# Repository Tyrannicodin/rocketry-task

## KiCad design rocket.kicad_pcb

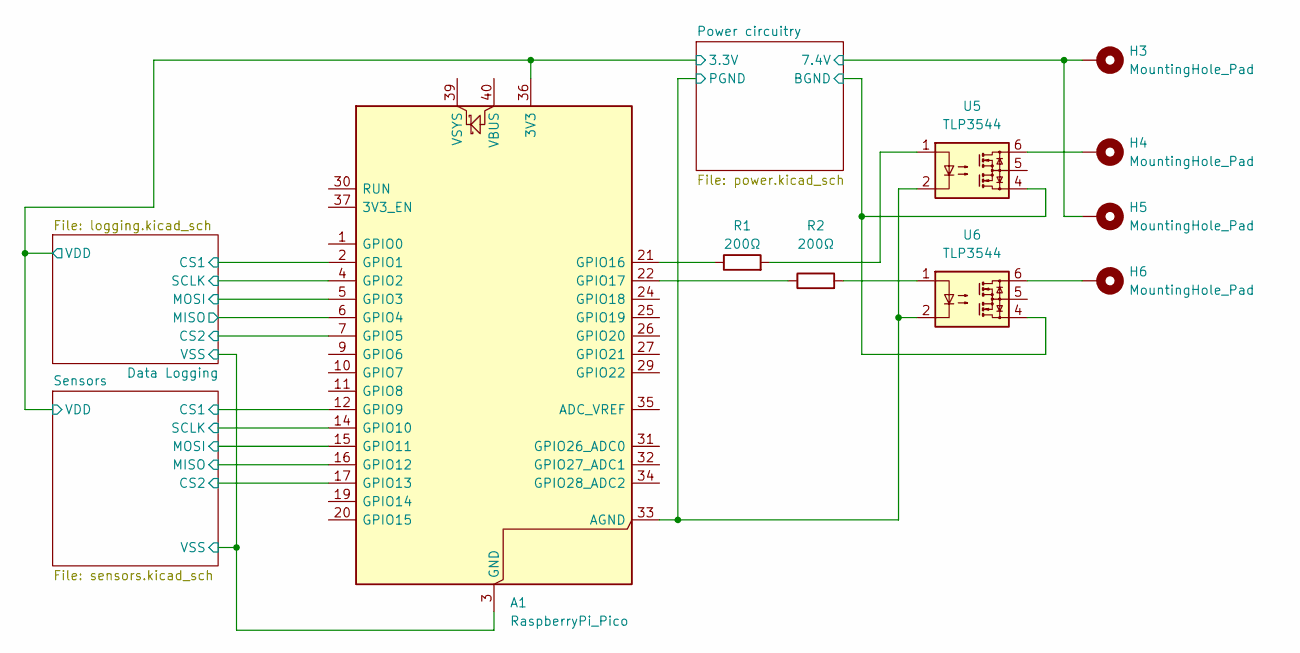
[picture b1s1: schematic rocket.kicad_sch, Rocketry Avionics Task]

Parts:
A1: RaspberryPi_Pico; RaspberryPi_Pico_Common_Unspecified
H3, H4, H5, H6: MountingHole_Pad; MountingHole_2.5mm_Pad
R1, R2: 200Ω; R_0201_0603Metric
U5, U6: TLP3544; DIP-6_W7.62mm

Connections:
/Data Logging/CS1: A1.2 (GPIO1); also elsewhere on the board
/Data Logging/CS2: A1.7 (GPIO5); also elsewhere on the board
/Data Logging/MISO: A1.6 (GPIO4); also elsewhere on the board
/Data Logging/MOSI: A1.5 (GPIO3); also elsewhere on the board
/Data Logging/SCLK: A1.4 (GPIO2); also elsewhere on the board
/Data Logging/VDD: A1.36 (3V3); also elsewhere on the board
/Data Logging/VSS: A1.3 (GND), A1.8 (GND), A1.13 (GND), A1.18 (GND), A1.23 (GND), A1.28 (GND), A1.38 (GND); also elsewhere on the board
/Power circuitry/7.4V: H3.1, H5.1; also elsewhere on the board
/Power circuitry/BGND: U5.4, U6.4; also elsewhere on the board
/Power circuitry/PGND: A1.33 (AGND), U5.2, U6.2; also elsewhere on the board
/Sensors/CS1: A1.12 (GPIO9); also elsewhere on the board
/Sensors/CS2: A1.17 (GPIO13); also elsewhere on the board
/Sensors/MISO: A1.16 (GPIO12); also elsewhere on the board
/Sensors/MOSI: A1.15 (GPIO11); also elsewhere on the board
/Sensors/SCLK: A1.14 (GPIO10); also elsewhere on the board
unnamed: A1.21 (GPIO16), R1.1
unnamed: A1.22 (GPIO17), R2.1
unnamed: H4.1, U5.6
unnamed: H6.1, U6.6
unnamed: R1.2, U5.1
unnamed: R2.2, U6.1

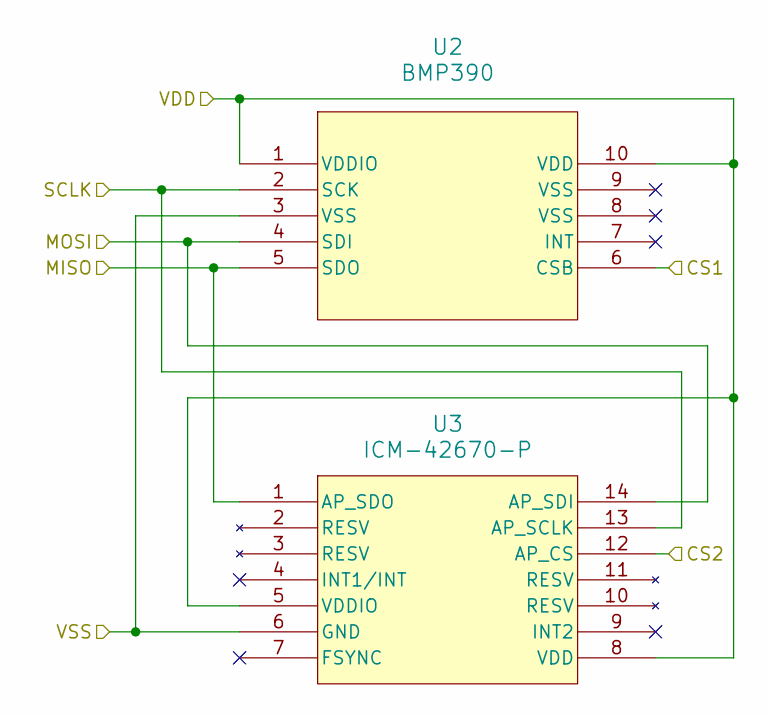
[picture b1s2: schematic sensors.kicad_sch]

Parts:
U2: BMP390; 10LGA_2X2X0p75_BOS
U3: ICM-42670-P; LGA14_2.5X3X0.76_IVS

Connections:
/Data Logging/VDD: U2.1 (VDDIO), U2.10 (VDD), U3.5 (VDDIO), U3.8 (VDD); also elsewhere on the board
/Data Logging/VSS: U2.3 (VSS), U3.6 (GND); also elsewhere on the board
/Sensors/CS1: U2.6 (CSB); also elsewhere on the board
/Sensors/CS2: U3.12 (AP_CS); also elsewhere on the board
/Sensors/MISO: U2.5 (SDO), U3.1 (AP_SDO); also elsewhere on the board
/Sensors/MOSI: U2.4 (SDI), U3.14 (AP_SDI); also elsewhere on the board
/Sensors/SCLK: U2.2 (SCK), U3.13 (AP_SCLK); also elsewhere on the board

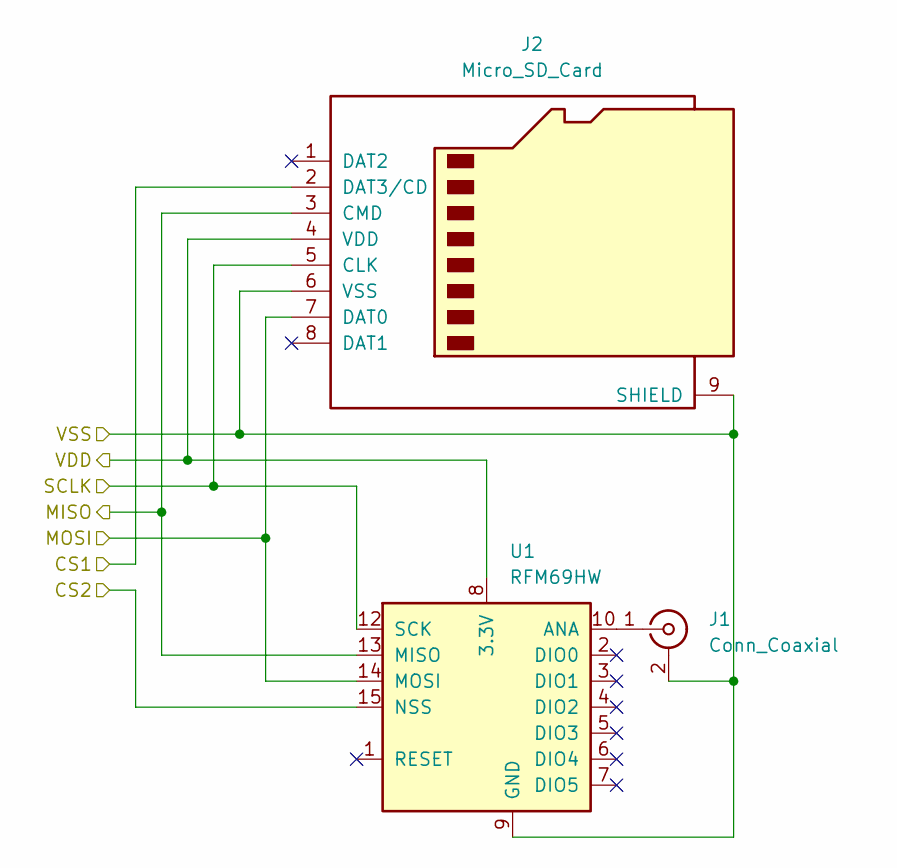
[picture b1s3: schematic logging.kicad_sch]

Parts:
J1: Conn_Coaxial; BNC_Amphenol_031-5539_Vertical
J2: Micro_SD_Card; microSD_HC_Wuerth_693072010801
U1: RFM69HW; HOPERF_RFM69HW

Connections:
/Data Logging/CS1: J2.2 (DAT3/CD); also elsewhere on the board
/Data Logging/CS2: U1.15 (NSS); also elsewhere on the board
/Data Logging/MISO: J2.3 (CMD), U1.13 (MISO); also elsewhere on the board
/Data Logging/MOSI: J2.7 (DAT0), U1.14 (MOSI); also elsewhere on the board
/Data Logging/SCLK: J2.5 (CLK), U1.12 (SCK); also elsewhere on the board
/Data Logging/VDD: J2.4 (VDD), U1.8 (3.3V); also elsewhere on the board
/Data Logging/VSS: J1.2 (Ext), J2.6 (VSS), J2.9 (SHIELD), U1.9 (GND), U1.11 (GND); also elsewhere on the board
unnamed: J1.1 (In), U1.10 (ANA)

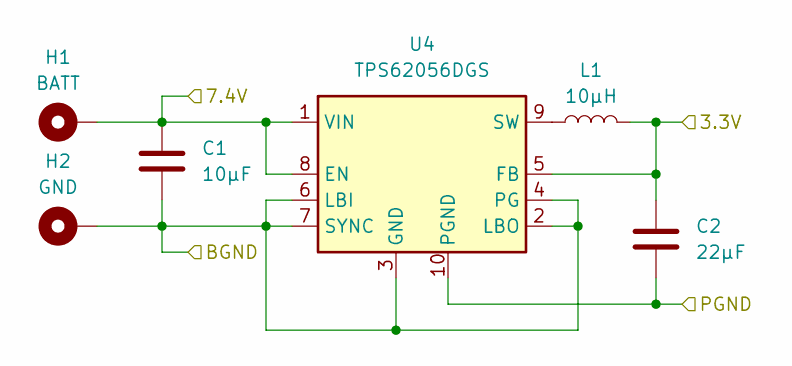
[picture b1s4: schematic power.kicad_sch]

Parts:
C1: 10µF; CP_Elec_4x3
C2: 22µF; CP_Elec_4x3
H1: BATT; MountingHole_2.5mm_Pad
H2: GND; MountingHole_2.5mm_Pad
L1: 10µH; L_12x12mm_H6mm
U4: TPS62056DGS; VSSOP-10_3x3mm_P0.5mm

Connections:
/Data Logging/VDD: C2.1, L1.2, U4.5 (FB); also elsewhere on the board
/Power circuitry/7.4V: C1.1, H1.1, U4.1 (VIN), U4.8 (EN); also elsewhere on the board
/Power circuitry/BGND: C1.2, H2.1, U4.2 (LBO), U4.3 (GND), U4.4 (PG), U4.6 (LBI), U4.7 (SYNC); also elsewhere on the board
/Power circuitry/PGND: C2.2, U4.10 (PGND); also elsewhere on the board
unnamed: L1.1, U4.9 (SW)

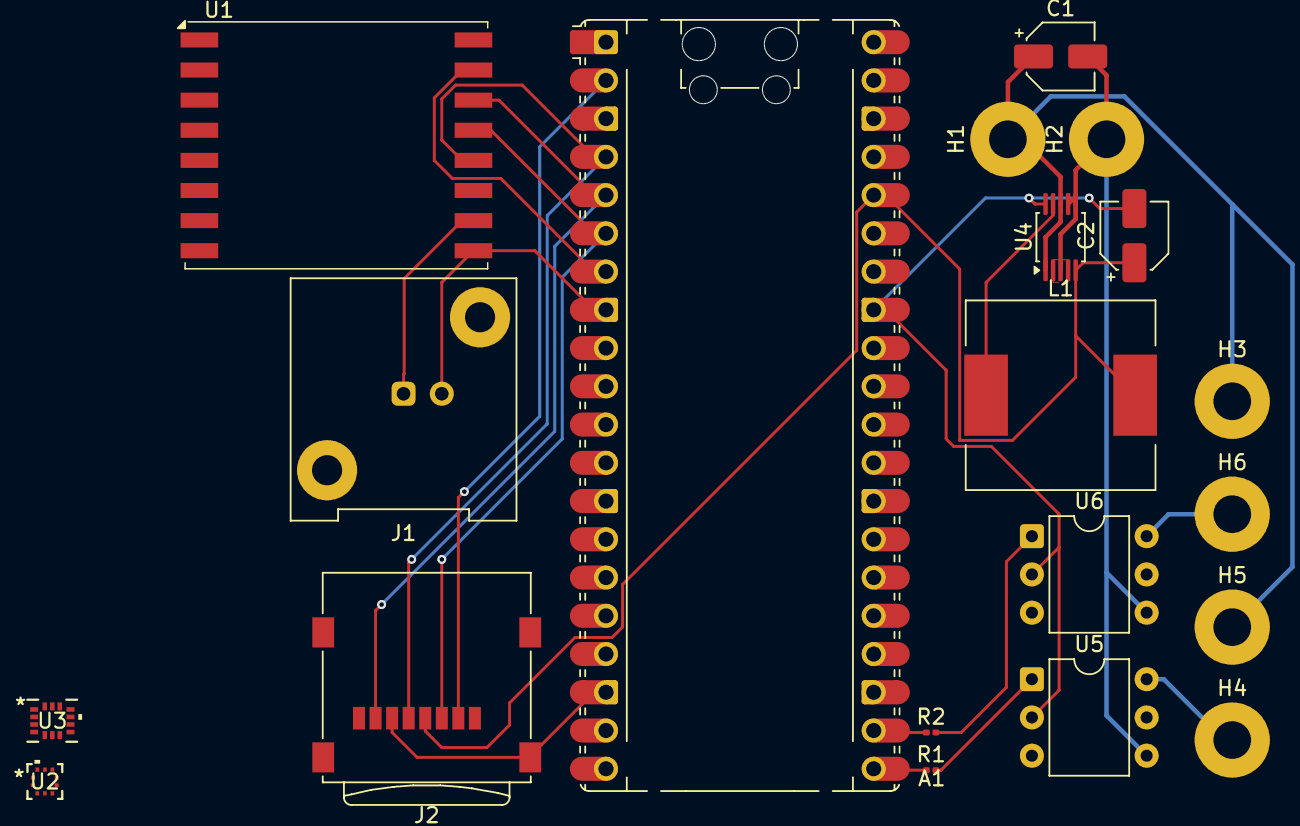
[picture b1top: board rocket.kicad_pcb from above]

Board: 2 copper layers, 20 parts (0 on the bottom side), 23 nets.

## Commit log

2025-10-15 Add BMP390
2025-10-15 Place components
2025-10-15 Logic level translators
2025-10-16 Add ICM-42670 chip
2025-10-16 Wiring
2025-10-16 Update footprint locations
2025-10-16 Power circuitry
2025-10-16 Update references and switch to higher power MOSFETS
2025-10-16 Begin PCB work
2025-10-17 PCB improvement
2025-10-17 External antenna
2025-10-18 A5, ignore write up files
2025-10-18 Add additional features
